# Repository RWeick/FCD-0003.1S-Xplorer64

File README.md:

# FCD-0003.1S-Xplorer64
Firmware, Schematic and Kicad PCB files for the Future Console Design Xplorer64. 

FCD implemented an address scrambling function in their CPLD in order to obfuscate the firmware. An unscrambled firmware is supplied and when it passes through the CPLD to be written to the eeproms, the data is scrambled and unrecognizable. With some analysis, I found a pattern in the scrambled firmware and was able to match it to originating locations in the unscrambled firmware. Many thanks to @Parasyte for deducing the scramble algorithm from that dataset. Firmware can now be scrambled and unscrambled at will using these functions:

function unscramble(addr) {
  return (( addr >> 4) & 0x001) |
         (( addr >> 8) & 0x002) |
         ((~addr >> 9) & 0x004) |
         (( addr >> 3) & 0x008) |
         (( addr >> 6) & 0x010) |
         (( addr >> 2) & 0x020) |
         ((~addr << 5) & 0x0c0) |
         ((~addr << 8) & 0x100) |
         ((~addr << 6) & 0x200) |
         ((~addr << 2) & 0x400) |
         (( addr << 6) & 0x800) |
         (addr & 0x1f000);
}

function scramble(addr) {
  return ((~addr >> 8) & 0x001) |
         ((~addr >> 5) & 0x006) |
         ((~addr >> 6) & 0x008) |
         (( addr << 4) & 0x010) |
         (( addr >> 6) & 0x020) |
         (( addr << 3) & 0x040) |
         (( addr << 2) & 0x080) |
         ((~addr >> 2) & 0x100) |
         (( addr << 8) & 0x200) |
         (( addr << 6) & 0x400) |
         ((~addr << 9) & 0x800) |
         (addr & 0x1f000);
}

Both scrambled and unscrambled firmwares are available in this repository.

I have included python scripts to automate the scramble and unscramble process. Usage is: py scramble.py <file.bin> and py unscramble.py <file.bin>
These will output a single file that is the result of the scrambling/unscrambling.

The entire firmware is mapped to 0x10400000 - 0x1043FFFF and can be easily read out with a Sanni Cart Reader at those addresses. Reading it out this way will produce an unscrambled firmware.

Writing firmware back requires the addresses and data to be transformed according to the scramble/unscramble functions listed above, and requires a read of 0x10760000 to initiate an even address write, or a read of 0x10770000 to initiate an odd address write, followed by the respective write to the transformed address, and ending with a read to 0x10740000. Even and odd writes are determined by dividing the original address in half, right shifting that data by 4, and checking parity. I've implemented this fully in the Sanni Cart Reader, and it can now program Xplorer 64 cartridges.

The parallel port comms are monitored at n64 PI address 0x1030_0000 and the default (nothing happening) data the xplorer 64 sees when nothing is connected to the parallel port is 0x0300_0300.

PCB Thickness: 1.2 mm

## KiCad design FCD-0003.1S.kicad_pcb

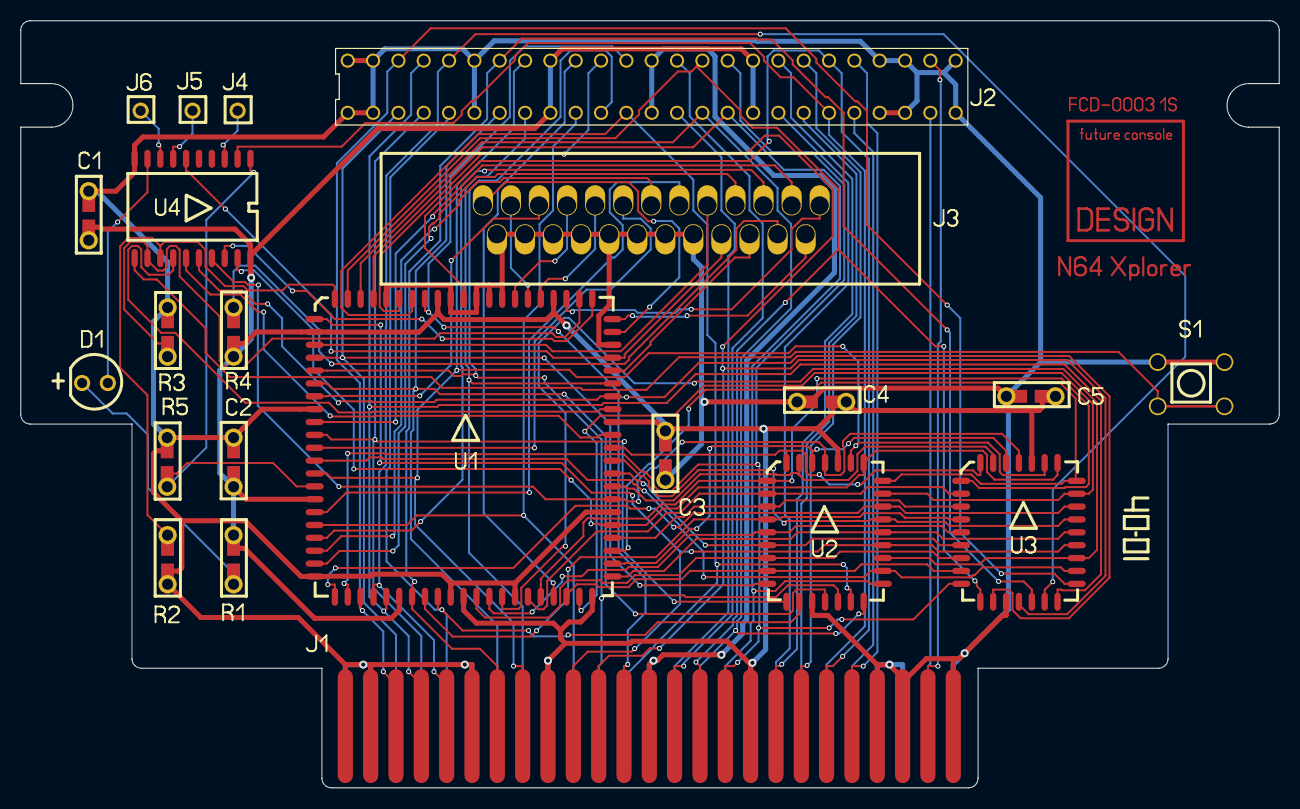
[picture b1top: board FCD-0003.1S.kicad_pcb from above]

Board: 2 copper layers, 124.2 x 75.7 mm, 22 parts (1 on the bottom side), 86 nets.

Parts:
C1, C2, C3, C4, C5: 100 nF; SMD Cap-Res
D1: Red LED; LED
J1: Cartridge Edge Connector
J2: Cartridge Slot; Upper Cartridge Slot
J3: DB25_Male; Parallel Port
J4, J5, J6: Jumper; Jumper Hole
R1: 221; SMD Cap-Res
R2, R3: 103; SMD Cap-Res
R4: 101; SMD Cap-Res
R5: Empty; SMD Cap-Res
S1: Push Button
U1: ATF1508AS-15JC84; ATMEL ATF1508AS
U2, U3: SST29LE010; SST 29LE010
U4: ATMEL AT90S1200-12SC

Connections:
/12V: J1.13 (12V), J1.38 (12V), J2.13 (12V), J2.38 (12V)
/A0: U1.51 (I/O), U2.12 (A0), U3.12 (A0)
/A1: U1.44 (I/O), U2.11 (A1), U3.11 (A1)
/A2: U1.62 (I/O/TCK), U2.10 (A2), U3.10 (A2)
/A3: U1.45 (I/O/PD2), U2.9 (A3), U3.9 (A3)
/A4: U1.40 (I/O), U2.8 (A4), U3.8 (A4)
/A5: U1.57 (I/O), U2.7 (A5), U3.7 (A5)
/A6: U1.48 (I/O), U2.6 (A6), U3.6 (A6)
/A7: U1.49 (I/O), U2.5 (A7), U3.5 (A7)
/A8: U1.33 (I/O), U2.27 (A8), U3.27 (A8)
/A9: U1.63 (I/O), U2.26 (A9), U3.26 (A9)
/A10: U1.46 (I/O), U2.23 (A10), U3.23 (A10)
/A11: U1.54 (I/O), U2.25 (A11), U3.25 (A11)
/A12: U1.64 (I/O), U2.4 (A12), U3.4 (A12)
/A13: U1.52 (I/O), U2.28 (A13), U3.28 (A13)
/A14: U1.56 (I/O), U2.29 (A14), U3.29 (A14)
/A15: U1.61 (I/O), U2.3 (A15), U3.3 (A15)
/A16: U1.55 (I/O), U2.2 (A16), U3.2 (A16)
/A17: U1.58 (I/O), U2.30 (N/C), U3.30 (N/C), U4.19 (PB7_(SCK))
/A18: U1.60 (I/O), U2.1 (N/C), U3.1 (N/C), U4.17 (PB5_(MOSI))
/AD0: J1.28 (AD0), J2.28 (AD0), U1.15 (I/O), U2.13 (D0)
/AD1: J1.29 (AD1), J2.29 (AD1), U1.21 (I/O), U2.14 (D1)
/AD2: J1.30 (AD2), J2.30 (AD2), U1.41 (I/O), U2.15 (D2)
/AD3: J1.32 (AD3), J2.32 (AD3), U1.17 (I/O), U2.17 (D3)
/AD4: J1.36 (AD4), J2.36 (AD4), U1.16 (I/O), U2.18 (D4)
/AD5: J1.37 (AD5), J2.37 (AD5), U1.5 (I/O), U2.19 (D5)
/AD6: J1.40 (AD6), J2.40 (AD6), U1.9 (I/O), U2.20 (D6)
/AD7: J1.41 (AD7), J2.41 (AD7), U1.8 (I/O), U2.21 (D7)
/AD8: J1.16 (AD8), J2.16 (AD8), U1.34 (I/O), U3.13 (D0)
/AD9: J1.15 (AD9), J2.15 (AD9), U1.10 (I/O), U3.14 (D1)
/AD10: J1.12 (AD10), J2.12 (AD10), U1.4 (I/O), U3.15 (D2)
/AD11: J1.11 (AD11), J2.11 (AD11), U1.6 (I/O), U3.17 (D3)
/AD12: J1.7 (AD12), J2.7 (AD12), U1.39 (I/O), U3.18 (D4)
/AD13: J1.5 (AD13), J2.5 (AD13), U1.36 (I/O), U3.19 (D5)
/AD14: J1.4 (AD14), J2.4 (AD14), U1.37 (I/O), U3.20 (D6)
/AD15: J1.3 (AD15), J2.3 (AD15), U1.35 (I/O), U3.21 (D7)
/ALE_H: J1.35 (ALE_H), J2.35 (ALE_H), U1.28 (I/O)
/ALE_L: J1.33 (ALE_L), J2.33 (ALE_L), U1.69 (I/O)
/Button: S1.3 (K), S1.4 (A), U4.11 (PD6)
/CIC_11: J1.19 (CIC_11), J2.19 (CIC_11)
/CIC_14: J1.43 (CIC_14), J2.43 (CIC_14)
/CIC_15: J1.18 (CIC_15), J2.18 (CIC_15)
/GND: C1.2, C2.2, C3.1, C4.1, C5.1, J1.1 (GND), J1.2 (GND), J1.6 (GND), J1.22 (GND), J1.23 (GND), J1.25 (GND), J1.26 (GND), J1.27 (GND), J1.31 (GND), J1.47 (GND), J1.48 (GND), J1.50 (GND), J2.1 (GND), J2.2 (GND), J2.6 (GND), J2.22 (GND), J2.23 (GND), J2.25 (GND), J2.26 (GND), J2.27 (GND), J2.31 (GND), J2.47 (GND), J2.48 (GND), J2.50 (GND), J3.18, J3.19, J3.20, J3.21, J3.22, J3.23, J3.24, J3.25, R2.1, R3.2, R5.2, S1.1, S1.2, U1.2 (Input/OE2/GCLK2), U1.7 (GND), U1.19 (GND), U1.32 (GND), U1.42 (GND), U1.47 (GND), U1.59 (GND), U1.72 (GND), U1.82 (GND), U1.83 (Input/GCLK1), U1.84 (Input/OE1), U2.16 (GND), U3.16 (GND), U4.10 (GND)
/INT1: J1.44 (/INT1), J2.44 (/INT1)
/LAUDIO: J1.24 (LAUDIO), J2.24 (LAUDIO)
/LED.Neg: D1.2 (A), U4.9 (PD5)
/LED.Pos: D1.1 (K), R1.1
/LPT.ACK: J3.10, U1.81 (I/O/GCLK3)
/LPT.Busy: J3.11, U1.18 (I/O)
/LPT.D0: J3.2, U1.20 (I/O)
/LPT.D1: J3.3, U1.29 (I/O)
/LPT.D2: J3.4, U1.31 (I/O)
/LPT.D3: J3.5, U1.14 (I/O/TDI)
/LPT.D4: J3.6, U1.27 (I/O)
/LPT.D5: J3.7, U1.30 (I/O)
/LPT.D6: J3.8, U1.22 (I/O)
/LPT.D7: J3.9, U1.79 (I/O)
/LPT.Error: J3.15, R4.2
/LPT.LineFeed: J3.14, U1.74 (I/O)
/LPT.PaperOut: J3.12, U1.80 (I/O)
/LPT.Reset: J3.16, U1.70 (I/O)
/LPT.SelPtr: J3.17, U1.71 (I/O/TDO), U4.6 ((INT0)_PD2)
/LPT.Select: J3.13, U1.73 (I/O)
/LPT.Strobe: J3.1, U1.77 (I/O)
/MCU.PB0: R3.1, U1.76 (I/O), U4.12 (PB0_(AIN0))
/MCU.PB1: R2.2, U1.11 (I/O), U4.13 (PB1_(AIN1))
/MCU.PB2: U1.67 (I/O), U4.14 (PB2)
/MCU.PB3: U1.65 (I/O), U4.15 (PB3)
/MCU.PB4: U1.68 (I/O), U4.16 (PB4)
/MCU.PB6: U1.75 (I/O), U4.18 (PB6_(MISO))
/MCU.Reset: R5.1, U1.25 (I/O), U4.1 (Reset)
/NMI: J1.45 (/NMI), J2.45 (/NMI), U4.2 (PD0)
/RAUDIO: J1.49 (RAUDIO), J2.49 (RAUDIO)
/SST.CE: U1.23 (I/O/TMS), U2.22 (CE#), U3.22 (CE#)
/S_DAT: J1.21 (EEPROM_DAT), J2.21 (EEPROM_DAT)
/UNUSED_Front: J1.14 (12V), J2.14 (12V)
/UNUSED_Rear: J1.39 (12V), J2.39 (12V)
/VCC: C1.1, C2.1, C3.2, C4.2, C5.2, J1.9 (3.3V), J1.17 (3.3V), J1.34 (3.3V), J1.42 (3.3V), J2.9 (3.3V), J2.17 (3.3V), J2.34 (3.3V), J2.42 (3.3V), R1.2, R4.1, U1.3 (VCCINT), U1.13 (VCCIO), U1.26 (VCCIO), U1.38 (VCCIO), U1.43 (VCCINT), U1.53 (VCCIO), U1.66 (VCCIO), U1.78 (VCCIO), U2.32 (VCC), U3.32 (VCC), U4.20 (VCC)
/Video_Sync: J1.46 (VIDEO_SYNC), J2.46 (VIDEO_SYNC)
//COLD_RESET: J1.20 (/ColdReset), J2.20 (/ColdReset), U1.1 (Input/GCLR)
//Read_Top: J2.10 (/RD), U1.50 (I/O)
//read_bottom: J1.10 (/RD), U1.12 (I/O/PD1), U2.24 (OE#), U3.24 (OE#)
//write: J1.8 (/WR), J2.8 (/WR), U1.24 (I/O), U2.31 (WE#), U3.31 (WE#)
unnamed: J4.1, U4.3 (PD1)
unnamed: J5.1, U4.7 (PD3)
unnamed: J6.1, U4.8 ((T0)_PD4)

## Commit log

2024-01-09 Add files via upload
    Thank you to Danhans42 for dumping this firmware! (1.000E 1772)
2024-01-30 Add files via upload
    Thank you Danhans42!
